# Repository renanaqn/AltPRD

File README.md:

# AltPRD
Desenvolvimento do projeto de Altímetro PRD v0 

Acabou que virou um outro produto completamente completo kk

## Como estava:

Esquemático do circuito:

Visão geral do layout PCB:

Visão 3D superior:

Visão 3D inferior:

## Como ficou:

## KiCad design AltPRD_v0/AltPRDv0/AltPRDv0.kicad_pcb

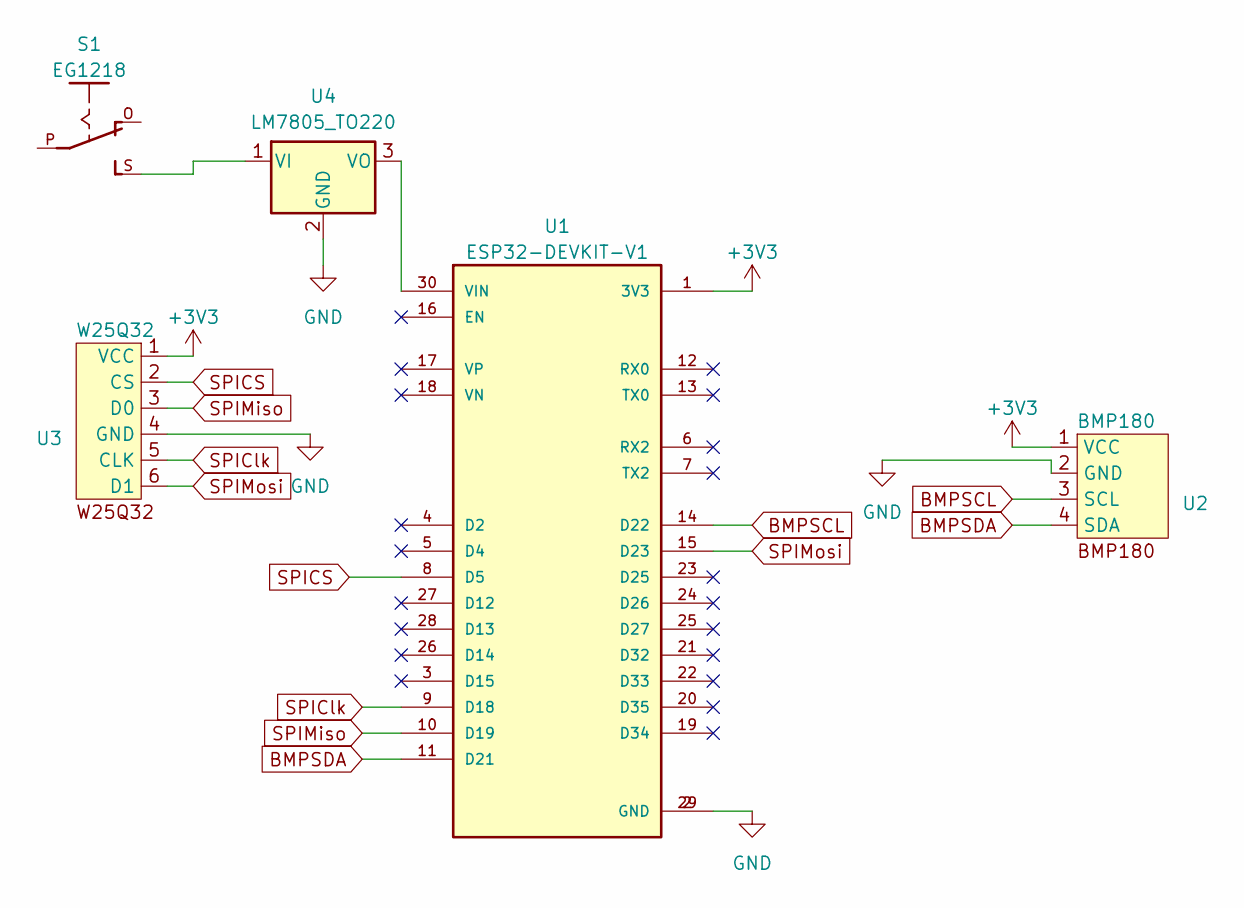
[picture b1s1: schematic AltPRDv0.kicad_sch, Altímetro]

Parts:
S1: EG1218
U1: ESP32-DEVKIT-V1; MODULE_ESP32_DEVKIT_V1; PARTREV N/A
U2: BMP180
U3: W25Q32
U4: LM7805_TO220; TO-220-3_Vertical

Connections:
+3V3: U1.1 (3V3), U2.1 (VCC), U3.1 (VCC)
BMPSCL: U1.14 (D22), U2.3 (SCL)
BMPSDA: U1.11 (D21), U2.4 (SDA)
GND: U1.2 (GND), U1.29 (GND), U2.2 (GND), U3.4 (GND), U4.2 (GND)
unnamed: U1.30 (VIN), U4.3 (VO)
unnamed: S1.S, U4.1 (VI)
SPICS: U1.8 (D5), U3.2 (CS)
SPIClk: U1.9 (D18), U3.5 (CLK)
SPIMiso: U1.10 (D19), U3.3 (D0)
SPIMosi: U1.15 (D23), U3.6 (D1)

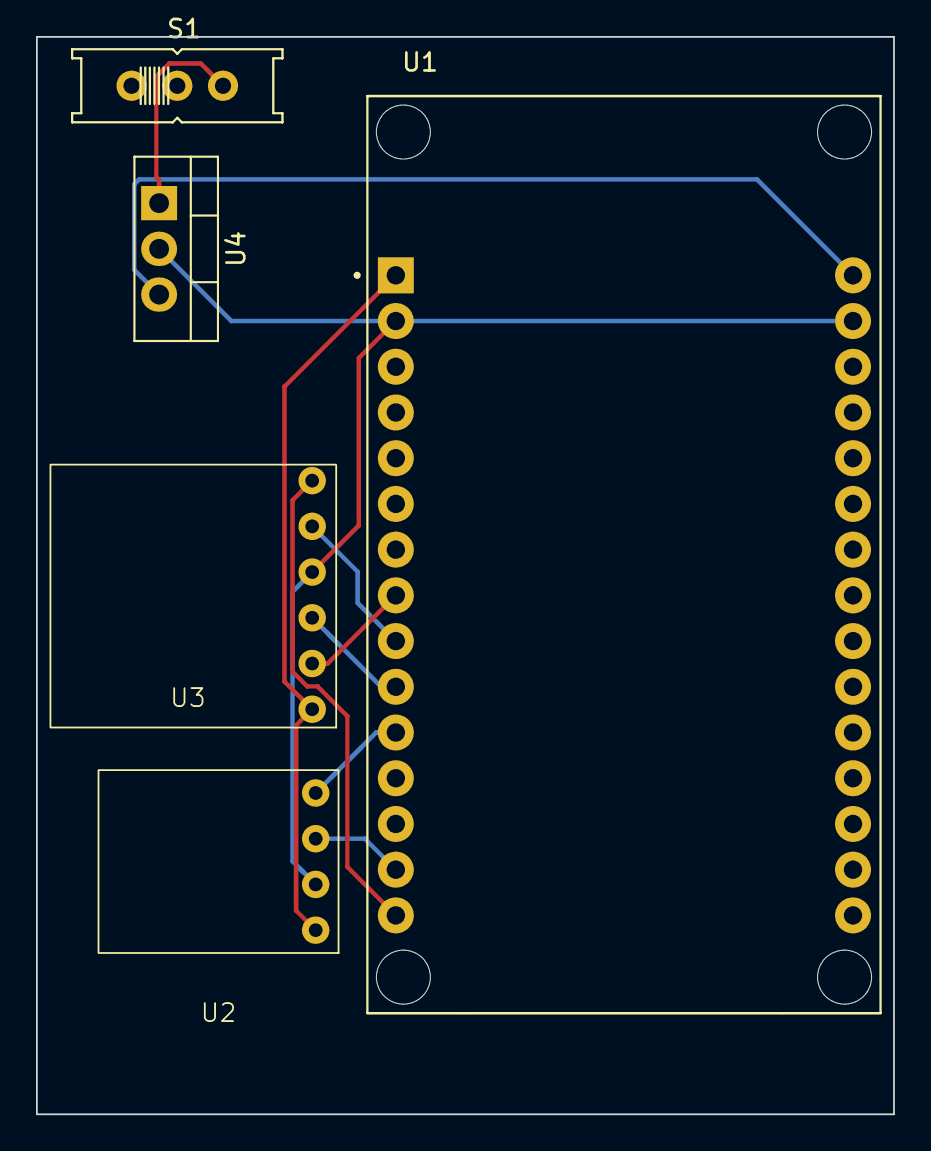
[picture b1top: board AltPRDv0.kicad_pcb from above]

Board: 2 copper layers, 47.6 x 59.9 mm, 5 parts (0 on the bottom side), 10 nets.

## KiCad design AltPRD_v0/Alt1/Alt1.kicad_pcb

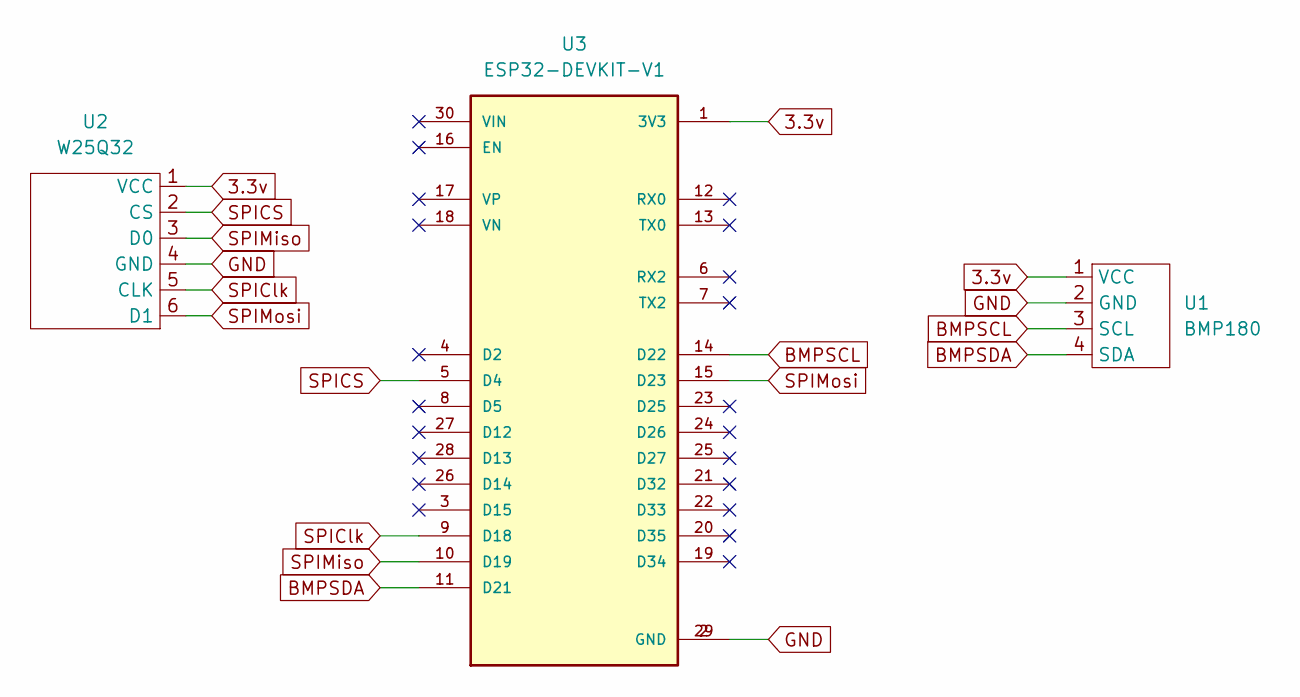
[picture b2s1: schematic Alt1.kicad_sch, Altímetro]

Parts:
U1: BMP180
U2: W25Q32; PinSocket_1x06_P2.54mm_Vertical
U3: ESP32-DEVKIT-V1; MODULE_ESP32_DEVKIT_V1; PARTREV N/A

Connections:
3.3v: U1.1 (VCC), U2.1 (VCC), U3.1 (3V3)
BMPSCL: U1.3 (SCL), U3.14 (D22)
BMPSDA: U1.4 (SDA), U3.11 (D21)
GND: U1.2 (GND), U2.4 (GND), U3.2 (GND), U3.29 (GND)
SPICS: U2.2 (CS), U3.5 (D4)
SPIClk: U2.5 (CLK), U3.9 (D18)
SPIMiso: U2.3 (D0), U3.10 (D19)
SPIMosi: U2.6 (D1), U3.15 (D23)

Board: 2 copper layers, 3 parts (0 on the bottom side), 8 nets, no tracks yet.

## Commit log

2023-03-28 Add files via upload
    rev: 0328
2023-03-28 Add files via upload
    Edição feita no dia 28/03 às 12h
2024-09-30 Atualizar o README.md
